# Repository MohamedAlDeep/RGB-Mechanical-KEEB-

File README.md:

# RGB Mechanical 75% KEEB

This is my custom made 75% rgb mechanical keyboard, it has per-key lights and hot swapable key switches.

> Why I made this project:

Because i have a laptop and i haven't had any actual separate keyboard experience, so i wanted to have one, and thought it would be nice for me to make my own for flexing on my fellows and solidify my PCB desiging knowledge.

--------------------------------

## BOM

| Id | Designator | Footprint PCB ONLY | Quantity | Designation | Supplier (LINK) | Price | Total |
|:---|:---|:---|:---|:---|:---|:---|:---|
| | New 104 Pcs Mechanical Keyboard Keycaps Set OEM Replacement Backlit ABS Purple White Key Cap for 61/87/104 Key Cherry MX Keycap | | 1.0 | | [Link](https://ar.aliexpress.com/item/1005005259313543.html?spm=a2g0o.productlist.main.7.158342deBxvvfk&algo_pvid=b131694e-62ef-4091-8a80-6c3d15457b02&algo_exp_id=b131694e-62ef-4091-8a80-6c3d15457b02-6&pdp_ext_f=%7B%22order%22%3A%22235%22%2C%22eval%22%3A%221%22%2C%22fromPage%22%3A%22search%22%7D&pdp_npi=6%40dis%21EGP%21567.85%21383.31%21%21%2110.77%217.27%21%4021015b7d17669196968648456e07cd%2112000032393281294%21sea%21EG%210%21ABX%211%210%21n_tag%3A-29910%3Bd%3Affa44bea%3Bm03_new_user%3A-29895%3BpisId%3A5000000187447427&curPageLogUid=Hf3LitEjKJwR&utparam-url=scene%3Asearch%7Cquery_from%3A%7Cx_object_id%3A1005005259313543%7C_p_origin_prod%3A&gatewayAdapt=glo2ara) | 8.06 | 8.06 |
| 6 | GATERON G Pro 3.0 Switches Pre-lubed 5 pinS RGB Linear for Gaming Mechanical Keyboard (Yellow) | | 1.0 | | [Link](https://ar.aliexpress.com/item/1005005862014771.html?spm=a2g0o.productlist.main.1.7c2e3773tPVyxZ&algo_pvid=362e47d1-3cf4-401f-8869-bb3fa592a69a&algo_exp_id=362e47d1-3cf4-401f-8869-bb3fa592a69a-0&pdp_ext_f=%7B%22order%22%3A%224%22%2C%22eval%22%3A%221%22%2C%22fromPage%22%3A%22search%22%7D&pdp_npi=6%40dis%21EGP%21564.67%21508.20%21%21%2175.00%2167.50%21%40212e508f17669195964155777efee1%2112000034613479091%21sea%21EG%210%21ABX%211%210%21n_tag%3A-29910%3Bd%3Affa44bea%3Bm03_new_user%3A-29895&curPageLogUid=BugaJfZUgWLk&utparam-url=scene%3Asearch%7Cquery_from%3A%7Cx_object_id%3A1005005862014771%7C_p_origin_prod%3A) | 10.69 | 10.69 |
| 7 | U2 | VSSOP-8_2.3x2mm_P0.5mm | 1.0 | 74LVCH2T45DC | [Link](https://jlcpcb.com/partdetail/Nexperia-74LVCH2T45DC125/C548924) | 0.564 | 0.564 |
| 8 | LED81,LED30,LED64,LED1,LED58,LED17,LED39,LED36,LED47,LED24,LED80,LED20,LED31,LED68,LED23,LED7,LED63,LED2,LED70,LED26,LED73,LED5,LED67,LED3,LED85,LED25,LED62,LED18,LED69,LED41,LED13,LED9,LED46,LED48,LED53,LED86,LED38,LED42,LED44,LED14,LED71,LED83,LED11,LED12,LED15,LED76,LED72,LED84,LED32,LED29,LED37,LED51,LED59,LED79,LED28,LED56,LED8,LED19,LED65,LED35,LED57,LED10,LED60,LED43,LED34,LED61,LED27,LED16,LED87,LED50,LED45,LED54,LED40,LED22,LED4,LED6,LED82,LED74,LED78,LED21,LED49,LED75,LED33,LED52 | LED_6028R | 84.0 | SK6812MINI-E | [Link](https://jlcpcb.com/partdetail/OPSCOOptoelectronics-SK6812MINIE/C5149201) | 0.0578 | 4.8552 |
| 9 | D77,D49,D82,D24,D37,D76,D83,D3,D81,D58,D72,D56,D40,D10,D45,D53,D20,D16,D28,D70,D1,D52,D38,D19,D11,D41,D50,D34,D9,D64,D22,D23,D47,D12,D43,D80,D2,D14,D17,D67,D7,D5,D71,D42,D78,D73,D68,D57,D33,D4,D65,D69,D13,D66,D27,D36,D74,D32,D15,D6,D84,D31,D8,D18,D61,D39,D46,D48,D30,D55,D35,D62,D60,D51,D59,D29,D25,D63,D21,D26,D44,D79,D75,D54 | D_0201_0603Metric | 84.0 | D | [Link](https://jlcpcb.com/partdetail/Comchip-CZRU52C2V7HF/C2886070) | 0.06 | 5.04 |
| 10 | R7,R6 | Resistor_0402 | 2.0 | 5.1k | [Link](https://jlcpcb.com/partdetail/26487-0402WGF1002TCE/C25744) | 0.0006 | 0.0012 |
| 11 | C10,C7,C3,C1,C2 | Capacitor_0402 | 5.0 | 100nF | [Link](https://jlcpcb.com/partdetail/1877-CL05B104KO5NNNC/C1525) | 0.0012 | 0.006 |
| 12 | J1 | USB_C_HRO_TYPE-C-31-M-12 | 1.0 | USB_C | [Link](https://jlcpcb.com/partdetail/Korean_HropartsElec-TYPE_C_31_M12/C165948) | 0.17 | 0.17 |
| 13 | U3 | ESD_SOT-23-6 | 1.0 | USBLC6-2SC6 | [Link](https://jlcpcb.com/partdetail/2790619-USBLC62SC6/C2687116) | 0.0368 | 0.0368 |
| 14 | C8 | Capacitor_0402 | 1.0 | 10nF | [Link](https://jlcpcb.com/partdetail/53938-CL05A105KA5NQNC/C52923) | 0.0029 | 0.0029 |
| 15 | U1 | Package_LQFP-48_7x7mm_P0.5 | 1.0 | STM32F072CBT6 | [Link](https://jlcpcb.com/partdetail/STMicroelectronics-STM32F072CBT6/C81720) | 1.3005 | 1.3005 |
| 16 | C12,C9,C13 | Capacitor_0402 | 3.0 | 1uF | [Link](https://jlcpcb.com/partdetail/15869-CL05B103KB5NNNC/C15195) | 0.0014 | 0.0042 |
| 17 | C11,C6 | Capacitor_0402 | 2.0 | 4.7uF | [Link](https://jlcpcb.com/partdetail/24469-CL05A475MP5NRNC/C23733) | 0.0046 | 0.0092 |
| 18 | U4 | Voltage_SOT-23 | 1.0 | XC6206 | [Link](https://jlcpcb.com/partdetail/TorexSemicon-XC6206P332MRG/C5446) | 0.0998 | 0.0998 |
| 19 | R5 | Resistor_0402 | 1.0 | 10k | [Link](https://jlcpcb.com/partdetail/26648-0402WGF5101TCE/C25905) | 0.0005 | 0.0005 |
| 20 | F1 | Fuse_0603 | 1.0 | 500mA | [Link](https://jlcpcb.com/partdetail/Hongda-2009T500mA250V/C529783) | 0.0551 | 0.0551 |
| 21 | SW343 | Button_TL3342 | 1.0 | SW_Push | [Link](https://jlcpcb.com/partdetail/Alpsalpine-SKQGABE010/C115351) | 0.0005 | 0.0005 |
| TOTAL IN USD | | | | | | | 31.5458 |

Add 15 usd for shipping and tax

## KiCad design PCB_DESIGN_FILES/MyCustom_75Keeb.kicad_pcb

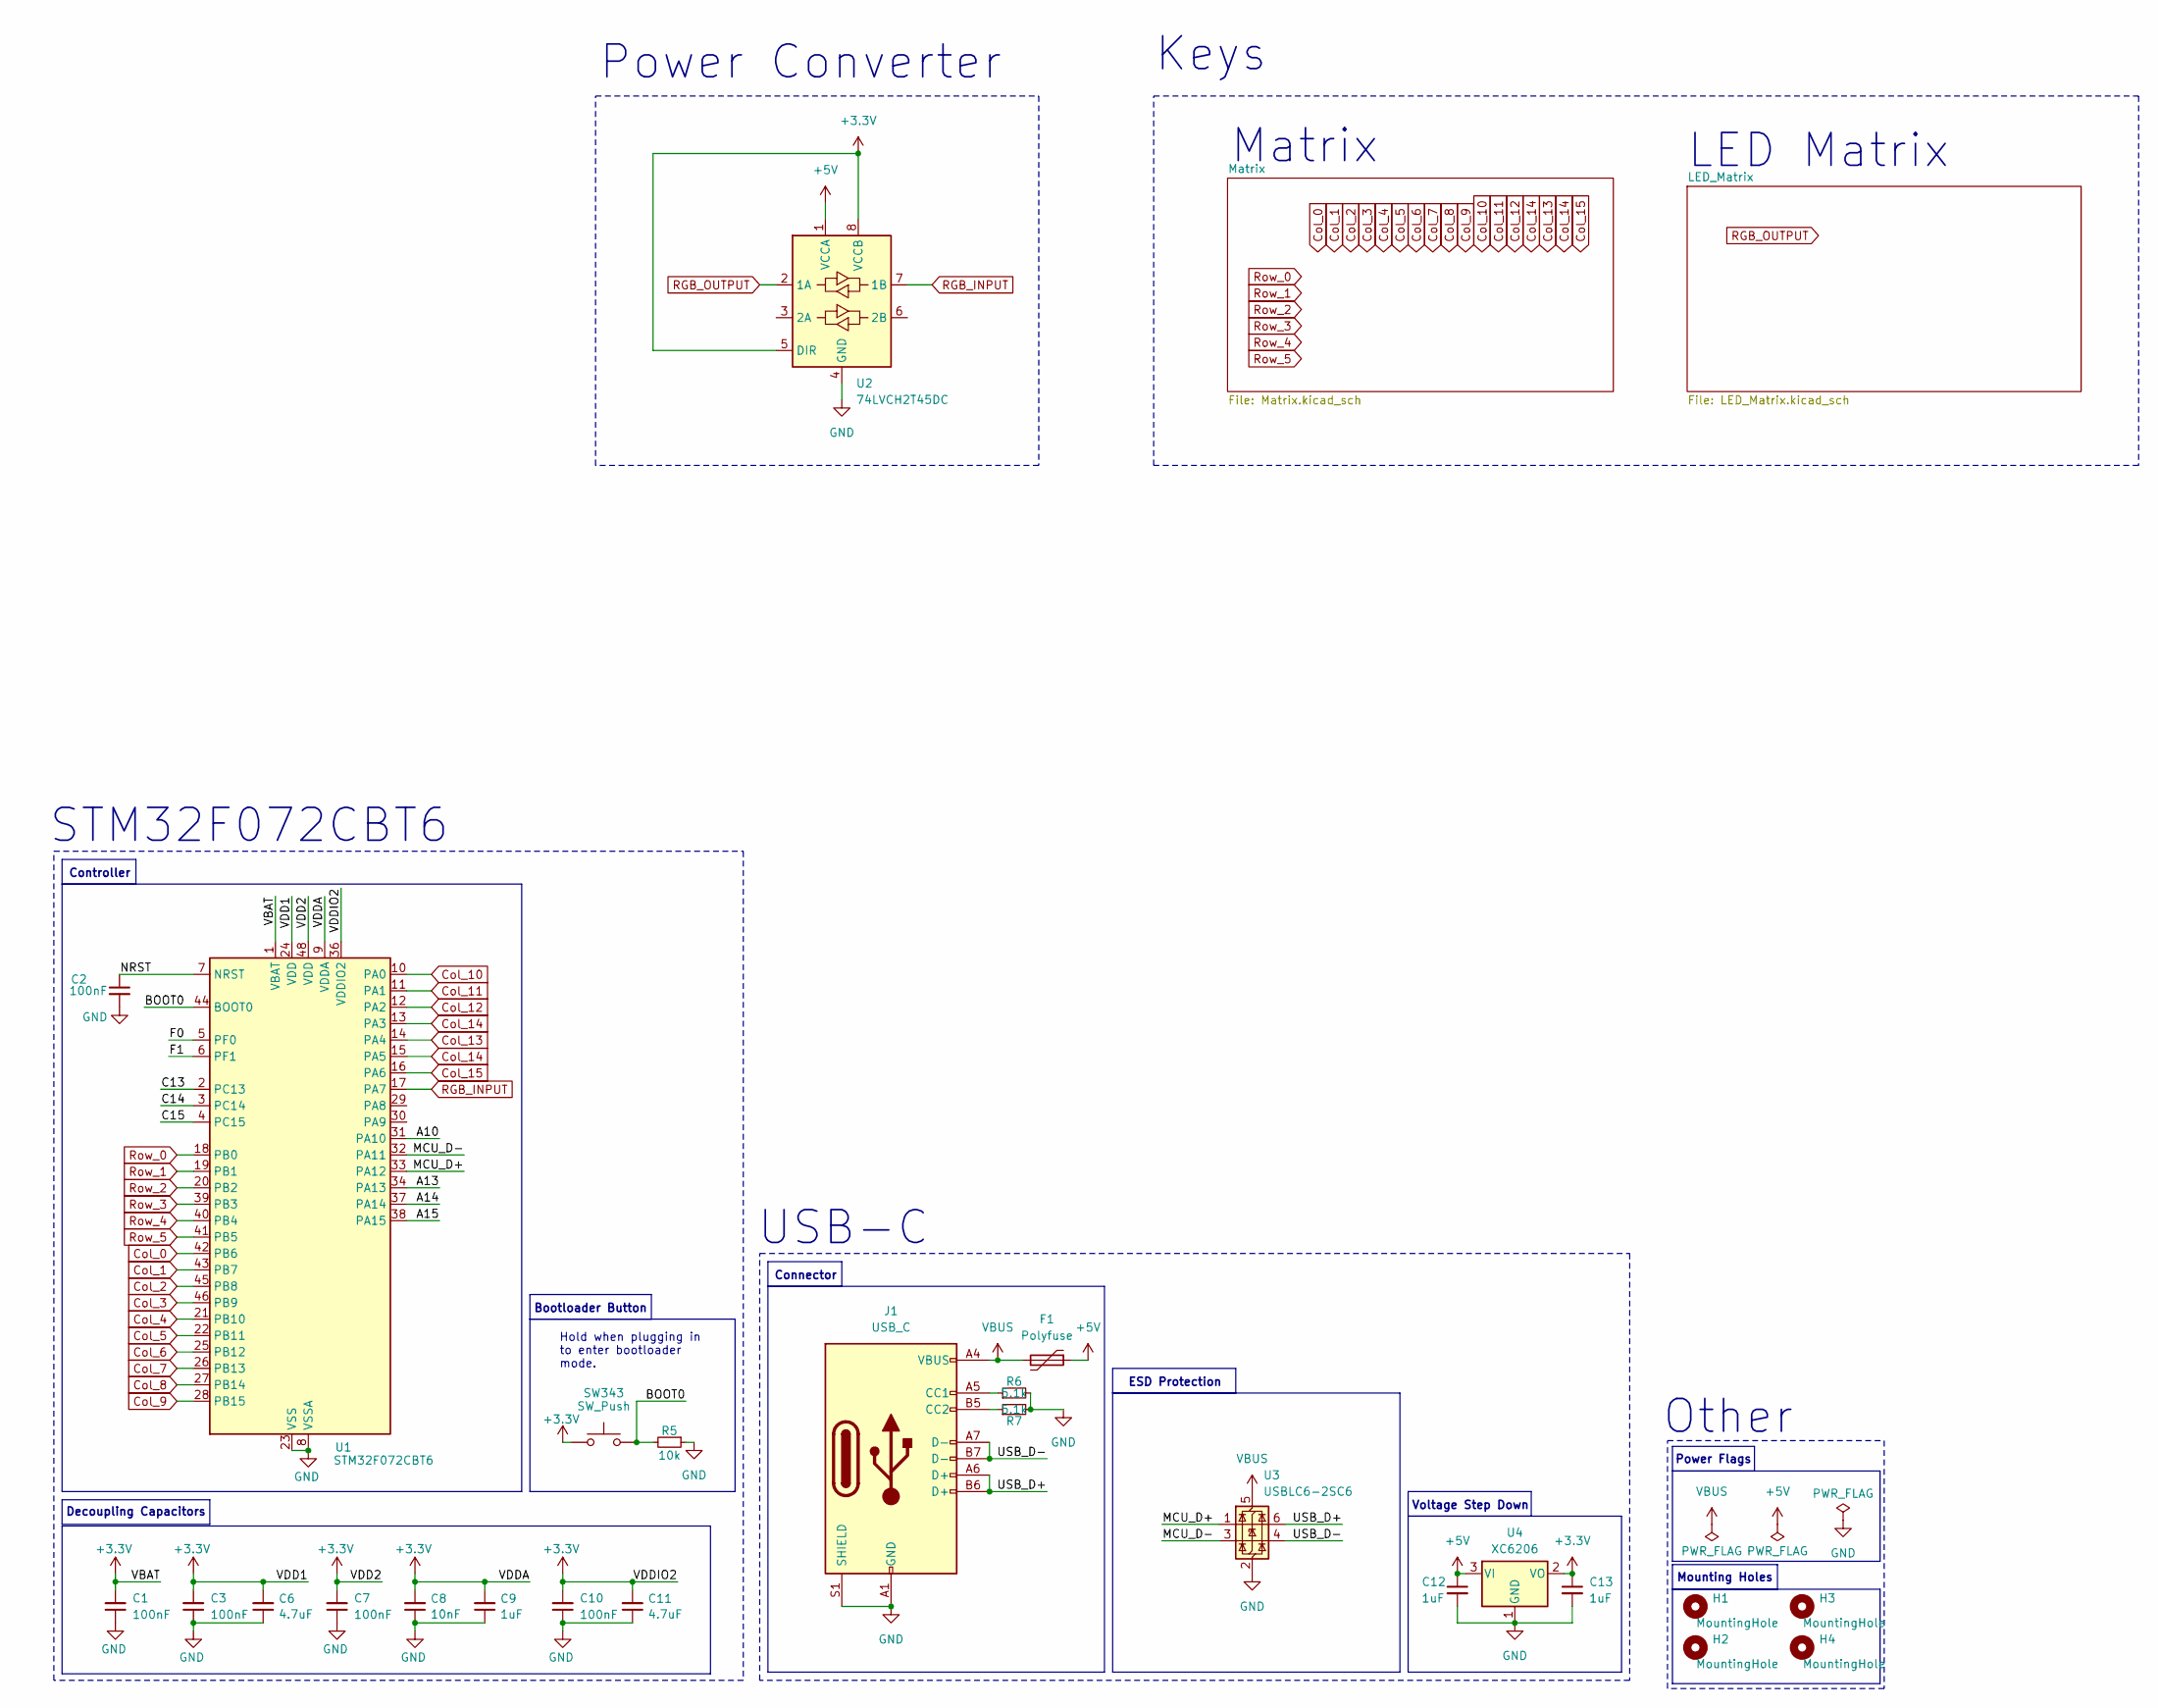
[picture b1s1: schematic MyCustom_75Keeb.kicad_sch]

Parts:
C1, C3, C7, C10: 100nF; Capacitor_0402; MPN CL05B104KB54PNC; LCSC C307331
C2: 100nF; Capacitor_0402; LCSC C307331
C6, C11: 4.7uF; Capacitor_0402; MPN CL05A475MP5NRNC; LCSC C23733
C8: 10nF; Capacitor_0402; MPN CL05B103KB5NNNC; LCSC C15195
C9: 1uF; Capacitor_0402; MPN CL05A105KA5NQNC; LCSC C52923
C12, C13: 1uF; Capacitor_0402; LCSC C52923
F1: Polyfuse; Fuse_Bourns_MF-RHT100
H1, H2, H3, H4: MountingHole; MountingHole_2.1mm
J1: USB_C; USB_C_HRO_TYPE-C-31-M-12; LCSC C165948
R5: 10k; Resistor_0402; LCSC C25744
R6, R7: 5.1k; Resistor_0402; LCSC C25905
SW343: SW_Push; Button_TL3342; LCSC C115351
U1: STM32F072CBT6; Package_LQFP-48_7x7mm_P0.5; LCSC C81720
U2: 74LVCH2T45DC; VSSOP-8_2.3x2mm_P0.5mm
U3: USBLC6-2SC6; ESD_SOT-23-6; LCSC C2827654
U4: XC6206; Voltage_SOT-23; LCSC C5446

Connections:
+3.3V: C1.2, C3.2, C6.2, C7.2, C8.2, C9.2, C10.2, C11.2, C13.1, SW343.1, U1.1 (VBAT), U1.9 (VDDA), U1.24 (VDD), U1.36 (VDDIO2), U1.48 (VDD), U2.5 (DIR), U2.8 (VCCB), U4.2 (VO)
/A10: U1.31 (PA10)
/A13: U1.34 (PA13)
/A14: U1.37 (PA14)
/A15: U1.38 (PA15)
/BOOT0: R5.2, SW343.2, U1.44 (BOOT0)
/C13: U1.2 (PC13)
/C14: U1.3 (PC14)
/C15: U1.4 (PC15)
/F0: U1.5 (PF0)
/F1: U1.6 (PF1)
/MCU_D+: U1.33 (PA12), U3.1 (I/O1)
/MCU_D-: U1.32 (PA11), U3.3 (I/O2)
/NRST: C2.1, U1.7 (NRST)
/USB_D+: J1.A6 (D+), J1.B6 (D+), U3.6 (I/O1)
/USB_D-: J1.A7 (D-), J1.B7 (D-), U3.4 (I/O2)
Col_0: U1.42 (PB6); also elsewhere on the board
Col_1: U1.43 (PB7); also elsewhere on the board
Col_2: U1.45 (PB8); also elsewhere on the board
Col_3: U1.46 (PB9); also elsewhere on the board
Col_4: U1.21 (PB10); also elsewhere on the board
Col_5: U1.22 (PB11); also elsewhere on the board
Col_6: U1.25 (PB12); also elsewhere on the board
Col_7: U1.26 (PB13); also elsewhere on the board
Col_8: U1.27 (PB14); also elsewhere on the board
Col_9: U1.28 (PB15); also elsewhere on the board
Col_10: U1.10 (PA0); also elsewhere on the board
Col_11: U1.11 (PA1); also elsewhere on the board
Col_12: U1.12 (PA2); also elsewhere on the board
Col_13: U1.14 (PA4); also elsewhere on the board
Col_14: U1.13 (PA3), U1.15 (PA5); also elsewhere on the board
Col_15: U1.16 (PA6); also elsewhere on the board
GND: C1.1, C2.2, C3.1, C6.1, C7.1, C8.1, C9.1, C10.1, C11.1, C12.2, C13.2, J1.A1 (GND), J1.A12 (GND), J1.B1 (GND), J1.B12 (GND), J1.S1 (SHIELD), R5.1, R6.2, R7.2, U1.8 (VSSA), U1.23 (VSS), U1.35 (VSS), U1.47 (VSS), U2.4 (GND), U3.2 (GND), U4.1 (GND); also elsewhere on the board
unnamed: J1.A5 (CC1), R6.1
unnamed: J1.B5 (CC2), R7.1
RGB_INPUT: U1.17 (PA7), U2.7 (1B)
RGB_OUTPUT: U2.2 (1A); also elsewhere on the board
Row_0: U1.18 (PB0); also elsewhere on the board
Row_1: U1.19 (PB1); also elsewhere on the board
Row_2: U1.20 (PB2); also elsewhere on the board
Row_3: U1.39 (PB3); also elsewhere on the board
Row_4: U1.40 (PB4); also elsewhere on the board
Row_5: U1.41 (PB5); also elsewhere on the board

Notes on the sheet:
Voltage Step Down
Other
USB-C
Keys
ESD Protection
STM32F072CBT6
Connector
Power Flags
Mounting Holes
Controller
Decoupling Capacitors
Power Converter
Matrix
LED Matrix
Bootloader Button
Hold when plugging in to enter bootloader mode.

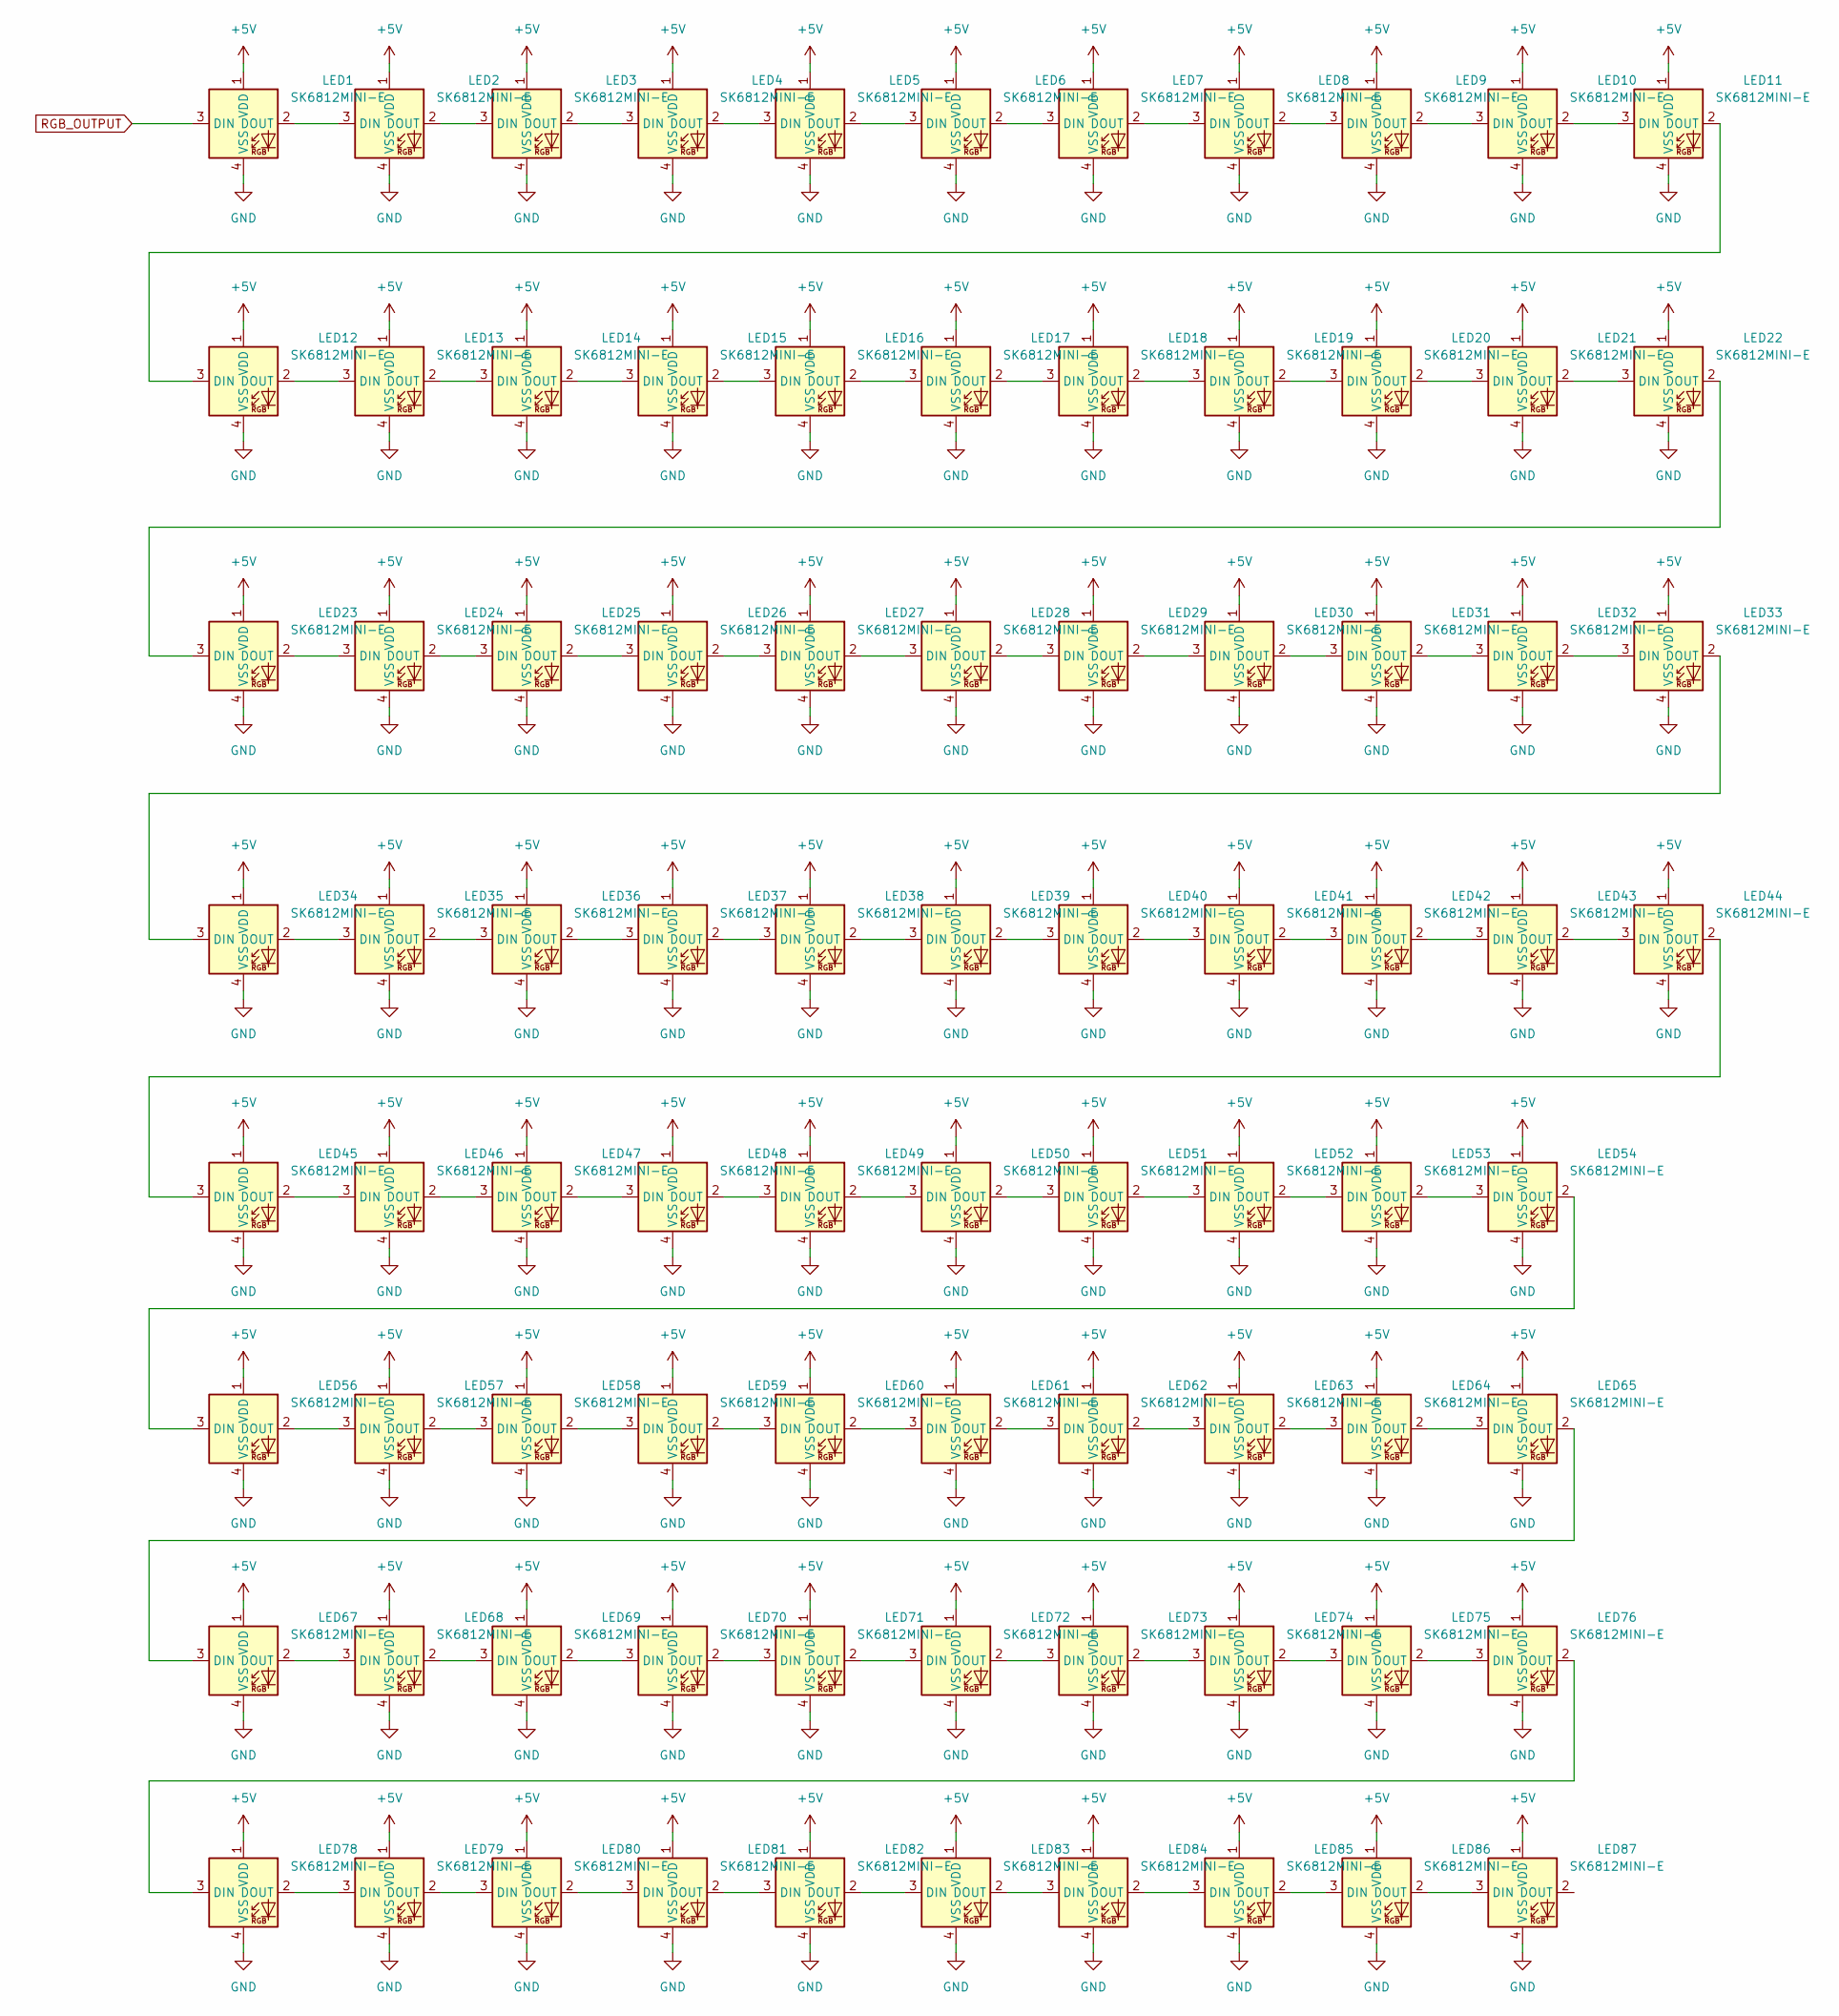
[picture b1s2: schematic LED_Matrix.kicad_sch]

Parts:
LED1, LED2, LED3, LED4, LED5, LED6, LED7, LED8, LED9, LED10, LED11, LED12, LED13, LED14, LED15, LED16, LED17, LED18, LED19, LED20, LED21, LED22, LED23, LED24, LED25, LED26, LED27, LED28, LED29, LED30, LED31, LED32, LED33, LED34, LED35, LED36, LED37, LED38, LED39, LED40, LED41, LED42, LED43, LED44, LED45, LED46, LED47, LED48, LED49, LED50, LED51, LED52, LED53, LED54, LED56, LED57, LED58, LED59, LED60, LED61, LED62, LED63, LED64, LED65, LED67, LED68, LED69, LED70, LED71, LED72, LED73, LED74, LED75, LED76, LED78, LED79, LED80, LED81, LED82, LED83, LED84, LED85, LED86, LED87: SK6812MINI-E; LED_6028R

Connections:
GND: LED1.4 (VSS), LED2.4 (VSS), LED3.4 (VSS), LED4.4 (VSS), LED5.4 (VSS), LED6.4 (VSS), LED7.4 (VSS), LED8.4 (VSS), LED9.4 (VSS), LED10.4 (VSS), LED11.4 (VSS), LED12.4 (VSS), LED13.4 (VSS), LED14.4 (VSS), LED15.4 (VSS), LED16.4 (VSS), LED17.4 (VSS), LED18.4 (VSS), LED19.4 (VSS), LED20.4 (VSS), LED21.4 (VSS), LED22.4 (VSS), LED23.4 (VSS), LED24.4 (VSS), LED25.4 (VSS), LED26.4 (VSS), LED27.4 (VSS), LED28.4 (VSS), LED29.4 (VSS), LED30.4 (VSS), LED31.4 (VSS), LED32.4 (VSS), LED33.4 (VSS), LED34.4 (VSS), LED35.4 (VSS), LED36.4 (VSS), LED37.4 (VSS), LED38.4 (VSS), LED39.4 (VSS), LED40.4 (VSS), LED41.4 (VSS), LED42.4 (VSS), LED43.4 (VSS), LED44.4 (VSS), LED45.4 (VSS), LED46.4 (VSS), LED47.4 (VSS), LED48.4 (VSS), LED49.4 (VSS), LED50.4 (VSS), LED51.4 (VSS), LED52.4 (VSS), LED53.4 (VSS), LED54.4 (VSS), LED56.4 (VSS), LED57.4 (VSS), LED58.4 (VSS), LED59.4 (VSS), LED60.4 (VSS), LED61.4 (VSS), LED62.4 (VSS), LED63.4 (VSS), LED64.4 (VSS), LED65.4 (VSS), LED67.4 (VSS), LED68.4 (VSS), LED69.4 (VSS), LED70.4 (VSS), LED71.4 (VSS), LED72.4 (VSS), LED73.4 (VSS), LED74.4 (VSS), LED75.4 (VSS), LED76.4 (VSS), LED78.4 (VSS), LED79.4 (VSS), LED80.4 (VSS), LED81.4 (VSS), LED82.4 (VSS), LED83.4 (VSS), LED84.4 (VSS), LED85.4 (VSS), LED86.4 (VSS), LED87.4 (VSS); also elsewhere on the board
unnamed: LED1.2 (DOUT), LED2.3 (DIN)
unnamed: LED2.2 (DOUT), LED3.3 (DIN)
unnamed: LED3.2 (DOUT), LED4.3 (DIN)
unnamed: LED4.2 (DOUT), LED5.3 (DIN)
unnamed: LED5.2 (DOUT), LED6.3 (DIN)
unnamed: LED6.2 (DOUT), LED7.3 (DIN)
unnamed: LED7.2 (DOUT), LED8.3 (DIN)
unnamed: LED8.2 (DOUT), LED9.3 (DIN)
unnamed: LED9.2 (DOUT), LED10.3 (DIN)
unnamed: LED10.2 (DOUT), LED11.3 (DIN)
unnamed: LED11.2 (DOUT), LED12.3 (DIN)
unnamed: LED12.2 (DOUT), LED13.3 (DIN)
unnamed: LED13.2 (DOUT), LED14.3 (DIN)
unnamed: LED14.2 (DOUT), LED15.3 (DIN)
unnamed: LED15.2 (DOUT), LED16.3 (DIN)
unnamed: LED16.2 (DOUT), LED17.3 (DIN)
unnamed: LED17.2 (DOUT), LED18.3 (DIN)
unnamed: LED18.2 (DOUT), LED19.3 (DIN)
unnamed: LED19.2 (DOUT), LED20.3 (DIN)
unnamed: LED20.2 (DOUT), LED21.3 (DIN)
unnamed: LED21.2 (DOUT), LED22.3 (DIN)
unnamed: LED22.2 (DOUT), LED23.3 (DIN)
unnamed: LED23.2 (DOUT), LED24.3 (DIN)
unnamed: LED24.2 (DOUT), LED25.3 (DIN)
unnamed: LED25.2 (DOUT), LED26.3 (DIN)
unnamed: LED26.2 (DOUT), LED27.3 (DIN)
unnamed: LED27.2 (DOUT), LED28.3 (DIN)
unnamed: LED28.2 (DOUT), LED29.3 (DIN)
unnamed: LED29.2 (DOUT), LED30.3 (DIN)
unnamed: LED30.2 (DOUT), LED31.3 (DIN)
unnamed: LED31.2 (DOUT), LED32.3 (DIN)
unnamed: LED32.2 (DOUT), LED33.3 (DIN)
unnamed: LED33.2 (DOUT), LED34.3 (DIN)
unnamed: LED34.2 (DOUT), LED35.3 (DIN)
unnamed: LED35.2 (DOUT), LED36.3 (DIN)
unnamed: LED36.2 (DOUT), LED37.3 (DIN)
unnamed: LED37.2 (DOUT), LED38.3 (DIN)
unnamed: LED38.2 (DOUT), LED39.3 (DIN)
unnamed: LED39.2 (DOUT), LED40.3 (DIN)
unnamed: LED40.2 (DOUT), LED41.3 (DIN)
unnamed: LED41.2 (DOUT), LED42.3 (DIN)
unnamed: LED42.2 (DOUT), LED43.3 (DIN)
unnamed: LED43.2 (DOUT), LED44.3 (DIN)
unnamed: LED44.2 (DOUT), LED45.3 (DIN)
unnamed: LED45.2 (DOUT), LED46.3 (DIN)
unnamed: LED46.2 (DOUT), LED47.3 (DIN)
unnamed: LED47.2 (DOUT), LED48.3 (DIN)
unnamed: LED48.2 (DOUT), LED49.3 (DIN)
unnamed: LED49.2 (DOUT), LED50.3 (DIN)
unnamed: LED50.2 (DOUT), LED51.3 (DIN)
unnamed: LED51.2 (DOUT), LED52.3 (DIN)
unnamed: LED52.2 (DOUT), LED53.3 (DIN)
unnamed: LED53.2 (DOUT), LED54.3 (DIN)
unnamed: LED54.2 (DOUT), LED56.3 (DIN)
unnamed: LED56.2 (DOUT), LED57.3 (DIN)
unnamed: LED57.2 (DOUT), LED58.3 (DIN)
unnamed: LED58.2 (DOUT), LED59.3 (DIN)
unnamed: LED59.2 (DOUT), LED60.3 (DIN)
unnamed: LED60.2 (DOUT), LED61.3 (DIN)
unnamed: LED61.2 (DOUT), LED62.3 (DIN)
unnamed: LED62.2 (DOUT), LED63.3 (DIN)
unnamed: LED63.2 (DOUT), LED64.3 (DIN)
unnamed: LED64.2 (DOUT), LED65.3 (DIN)
unnamed: LED65.2 (DOUT), LED67.3 (DIN)
unnamed: LED67.2 (DOUT), LED68.3 (DIN)
unnamed: LED68.2 (DOUT), LED69.3 (DIN)
unnamed: LED69.2 (DOUT), LED70.3 (DIN)
unnamed: LED70.2 (DOUT), LED71.3 (DIN)
unnamed: LED71.2 (DOUT), LED72.3 (DIN)
unnamed: LED72.2 (DOUT), LED73.3 (DIN)
unnamed: LED73.2 (DOUT), LED74.3 (DIN)
unnamed: LED74.2 (DOUT), LED75.3 (DIN)
unnamed: LED75.2 (DOUT), LED76.3 (DIN)
unnamed: LED76.2 (DOUT), LED78.3 (DIN)
unnamed: LED78.2 (DOUT), LED79.3 (DIN)
unnamed: LED79.2 (DOUT), LED80.3 (DIN)
unnamed: LED80.2 (DOUT), LED81.3 (DIN)
unnamed: LED81.2 (DOUT), LED82.3 (DIN)
unnamed: LED82.2 (DOUT), LED83.3 (DIN)
unnamed: LED83.2 (DOUT), LED84.3 (DIN)
unnamed: LED84.2 (DOUT), LED85.3 (DIN)
unnamed: LED85.2 (DOUT), LED86.3 (DIN)
unnamed: LED86.2 (DOUT), LED87.3 (DIN)
RGB_OUTPUT: LED1.3 (DIN); also elsewhere on the board

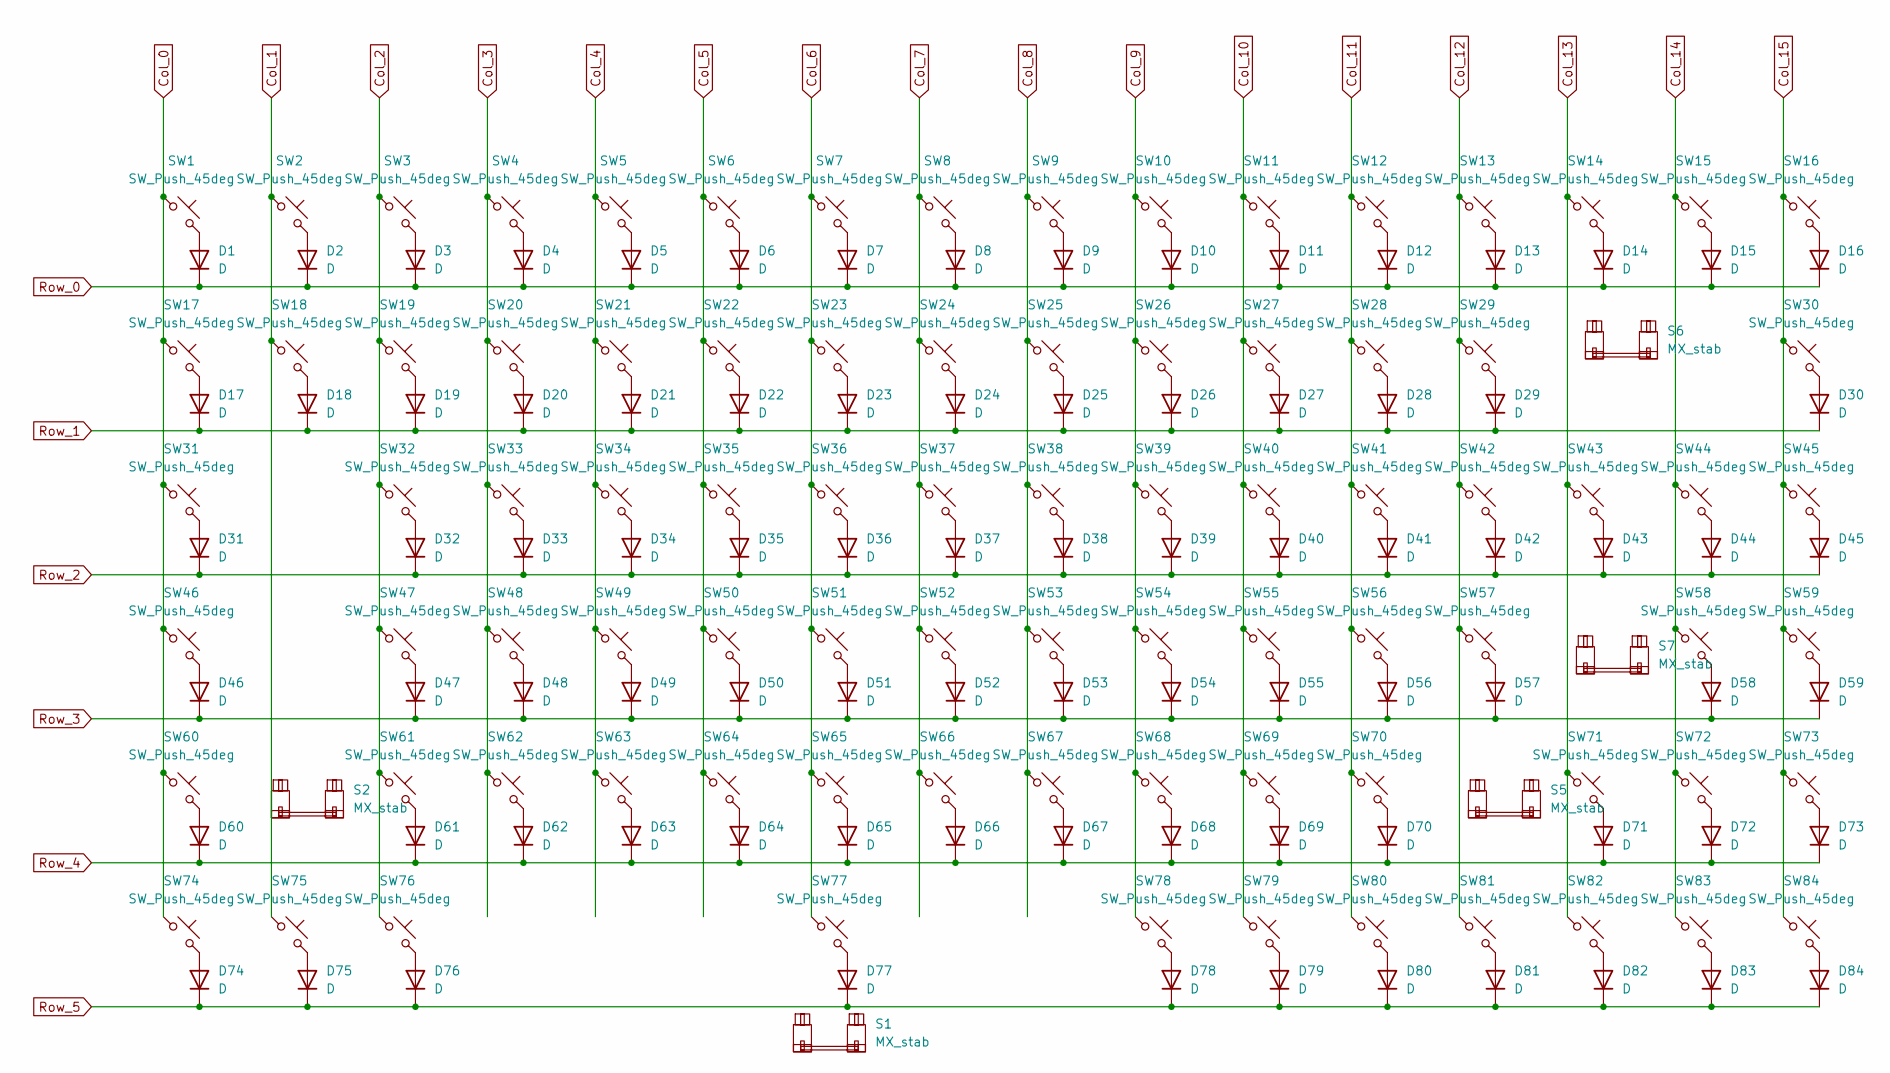
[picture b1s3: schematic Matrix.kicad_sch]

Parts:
D1, D2, D3, D4, D5, D6, D7, D8, D9, D10, D11, D12, D13, D14, D15, D16, D17, D18, D19, D20, D21, D22, D23, D24, D25, D26, D27, D28, D29, D30, D31, D32, D33, D34, D35, D36, D37, D38, D39, D40, D41, D42, D43, D44, D45, D46, D47, D48, D49, D50, D51, D52, D53, D54, D55, D56, D57, D58, D59, D60, D61, D62, D63, D64, D65, D66, D67, D68, D69, D70, D71, D72, D73, D74, D75, D76, D77, D78, D79, D80, D81, D82, D83, D84: D; D_0201_0603Metric
S1: MX_stab; STAB_MX_P_6.25u
S2: MX_stab; STAB_MX_P_2.25u
S5: MX_stab; STAB_MX_2u
S6: MX_stab; STAB_MX_P_2u
S7: MX_stab; STAB_MX_2.25u
SW1, SW2, SW3, SW4, SW5, SW6, SW7, SW8, SW9, SW10, SW11, SW12, SW13, SW14, SW15, SW16, SW17, SW18, SW19, SW20, SW21, SW22, SW23, SW24, SW25, SW26, SW27, SW28, SW29, SW30, SW31, SW32, SW33, SW34, SW35, SW36, SW37, SW38, SW39, SW40, SW41, SW42, SW43, SW44, SW45, SW46, SW47, SW48, SW49, SW50, SW51, SW52, SW53, SW54, SW55, SW56, SW57, SW58, SW59, SW60, SW61, SW62, SW63, SW64, SW65, SW66, SW67, SW68, SW69, SW70, SW71, SW72, SW73, SW74, SW75, SW76, SW77, SW78, SW79, SW80, SW81, SW82, SW83, SW84: SW_Push_45deg; SW_Cherry_MX_PCB_1.00u

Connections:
Col_0: SW1.1, SW17.1, SW31.1, SW46.1, SW60.1, SW74.1; also elsewhere on the board
Col_1: SW2.1, SW18.1, SW75.1; also elsewhere on the board
Col_2: SW3.1, SW19.1, SW32.1, SW47.1, SW61.1, SW76.1; also elsewhere on the board
Col_3: SW4.1, SW20.1, SW33.1, SW48.1, SW62.1; also elsewhere on the board
Col_4: SW5.1, SW21.1, SW34.1, SW49.1, SW63.1; also elsewhere on the board
Col_5: SW6.1, SW22.1, SW35.1, SW50.1, SW64.1; also elsewhere on the board
Col_6: SW7.1, SW23.1, SW36.1, SW51.1, SW65.1, SW77.1; also elsewhere on the board
Col_7: SW8.1, SW24.1, SW37.1, SW52.1, SW66.1; also elsewhere on the board
Col_8: SW9.1, SW25.1, SW38.1, SW53.1, SW67.1; also elsewhere on the board
Col_9: SW10.1, SW26.1, SW39.1, SW54.1, SW68.1, SW78.1; also elsewhere on the board
Col_10: SW11.1, SW27.1, SW40.1, SW55.1, SW69.1, SW79.1; also elsewhere on the board
Col_11: SW12.1, SW28.1, SW41.1, SW56.1, SW70.1, SW80.1; also elsewhere on the board
Col_12: SW13.1, SW29.1, SW42.1, SW57.1, SW81.1; also elsewhere on the board
Col_13: SW14.1, SW43.1, SW71.1, SW82.1; also elsewhere on the board
Col_14: SW15.1, SW44.1, SW58.1, SW72.1, SW83.1; also elsewhere on the board
Col_15: SW16.1, SW30.1, SW45.1, SW59.1, SW73.1, SW84.1; also elsewhere on the board
unnamed: D1.2 (A), SW1.2
unnamed: D2.2 (A), SW2.2
unnamed: D3.2 (A), SW3.2
unnamed: D4.2 (A), SW4.2
unnamed: D5.2 (A), SW5.2
unnamed: D6.2 (A), SW6.2
unnamed: D7.2 (A), SW7.2
unnamed: D8.2 (A), SW8.2
unnamed: D9.2 (A), SW9.2
unnamed: D10.2 (A), SW10.2
unnamed: D11.2 (A), SW11.2
unnamed: D12.2 (A), SW12.2
unnamed: D13.2 (A), SW13.2
unnamed: D14.2 (A), SW14.2
unnamed: D15.2 (A), SW15.2
unnamed: D16.2 (A), SW16.2
unnamed: D17.2 (A), SW17.2
unnamed: D18.2 (A), SW18.2
unnamed: D19.2 (A), SW19.2
unnamed: D20.2 (A), SW20.2
unnamed: D21.2 (A), SW21.2
unnamed: D22.2 (A), SW22.2
unnamed: D23.2 (A), SW23.2
unnamed: D24.2 (A), SW24.2
unnamed: D25.2 (A), SW25.2
unnamed: D26.2 (A), SW26.2
unnamed: D27.2 (A), SW27.2
unnamed: D28.2 (A), SW28.2
unnamed: D29.2 (A), SW29.2
unnamed: D30.2 (A), SW30.2
unnamed: D31.2 (A), SW31.2
unnamed: D32.2 (A), SW32.2
unnamed: D33.2 (A), SW33.2
unnamed: D34.2 (A), SW34.2
unnamed: D35.2 (A), SW35.2
unnamed: D36.2 (A), SW36.2
unnamed: D37.2 (A), SW37.2
unnamed: D38.2 (A), SW38.2
unnamed: D39.2 (A), SW39.2
unnamed: D40.2 (A), SW40.2
unnamed: D41.2 (A), SW41.2
unnamed: D42.2 (A), SW42.2
unnamed: D43.2 (A), SW43.2
unnamed: D44.2 (A), SW44.2
unnamed: D45.2 (A), SW45.2
unnamed: D46.2 (A), SW46.2
unnamed: D47.2 (A), SW47.2
unnamed: D48.2 (A), SW48.2
unnamed: D49.2 (A), SW49.2
unnamed: D50.2 (A), SW50.2
unnamed: D51.2 (A), SW51.2
unnamed: D52.2 (A), SW52.2
unnamed: D53.2 (A), SW53.2
unnamed: D54.2 (A), SW54.2
unnamed: D55.2 (A), SW55.2
unnamed: D56.2 (A), SW56.2
unnamed: D57.2 (A), SW57.2
unnamed: D58.2 (A), SW58.2
unnamed: D59.2 (A), SW59.2
unnamed: D60.2 (A), SW60.2
unnamed: D61.2 (A), SW61.2
unnamed: D62.2 (A), SW62.2
unnamed: D63.2 (A), SW63.2
unnamed: D64.2 (A), SW64.2
unnamed: D65.2 (A), SW65.2
unnamed: D66.2 (A), SW66.2
unnamed: D67.2 (A), SW67.2
unnamed: D68.2 (A), SW68.2
unnamed: D69.2 (A), SW69.2
unnamed: D70.2 (A), SW70.2
unnamed: D71.2 (A), SW71.2
unnamed: D72.2 (A), SW72.2
unnamed: D73.2 (A), SW73.2
unnamed: D74.2 (A), SW74.2
unnamed: D75.2 (A), SW75.2
unnamed: D76.2 (A), SW76.2
unnamed: D77.2 (A), SW77.2
unnamed: D78.2 (A), SW78.2
unnamed: D79.2 (A), SW79.2
unnamed: D80.2 (A), SW80.2
unnamed: D81.2 (A), SW81.2
unnamed: D82.2 (A), SW82.2
unnamed: D83.2 (A), SW83.2
unnamed: D84.2 (A), SW84.2
Row_0: D1.1 (K), D2.1 (K), D3.1 (K), D4.1 (K), D5.1 (K), D6.1 (K), D7.1 (K), D8.1 (K), D9.1 (K), D10.1 (K), D11.1 (K), D12.1 (K), D13.1 (K), D14.1 (K), D15.1 (K), D16.1 (K); also elsewhere on the board
Row_1: D17.1 (K), D18.1 (K), D19.1 (K), D20.1 (K), D21.1 (K), D22.1 (K), D23.1 (K), D24.1 (K), D25.1 (K), D26.1 (K), D27.1 (K), D28.1 (K), D29.1 (K), D30.1 (K); also elsewhere on the board
Row_2: D31.1 (K), D32.1 (K), D33.1 (K), D34.1 (K), D35.1 (K), D36.1 (K), D37.1 (K), D38.1 (K), D39.1 (K), D40.1 (K), D41.1 (K), D42.1 (K), D43.1 (K), D44.1 (K), D45.1 (K); also elsewhere on the board
Row_3: D46.1 (K), D47.1 (K), D48.1 (K), D49.1 (K), D50.1 (K), D51.1 (K), D52.1 (K), D53.1 (K), D54.1 (K), D55.1 (K), D56.1 (K), D57.1 (K), D58.1 (K), D59.1 (K); also elsewhere on the board
Row_4: D60.1 (K), D61.1 (K), D62.1 (K), D63.1 (K), D64.1 (K), D65.1 (K), D66.1 (K), D67.1 (K), D68.1 (K), D69.1 (K), D70.1 (K), D71.1 (K), D72.1 (K), D73.1 (K); also elsewhere on the board
Row_5: D74.1 (K), D75.1 (K), D76.1 (K), D77.1 (K), D78.1 (K), D79.1 (K), D80.1 (K), D81.1 (K), D82.1 (K), D83.1 (K), D84.1 (K); also elsewhere on the board

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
